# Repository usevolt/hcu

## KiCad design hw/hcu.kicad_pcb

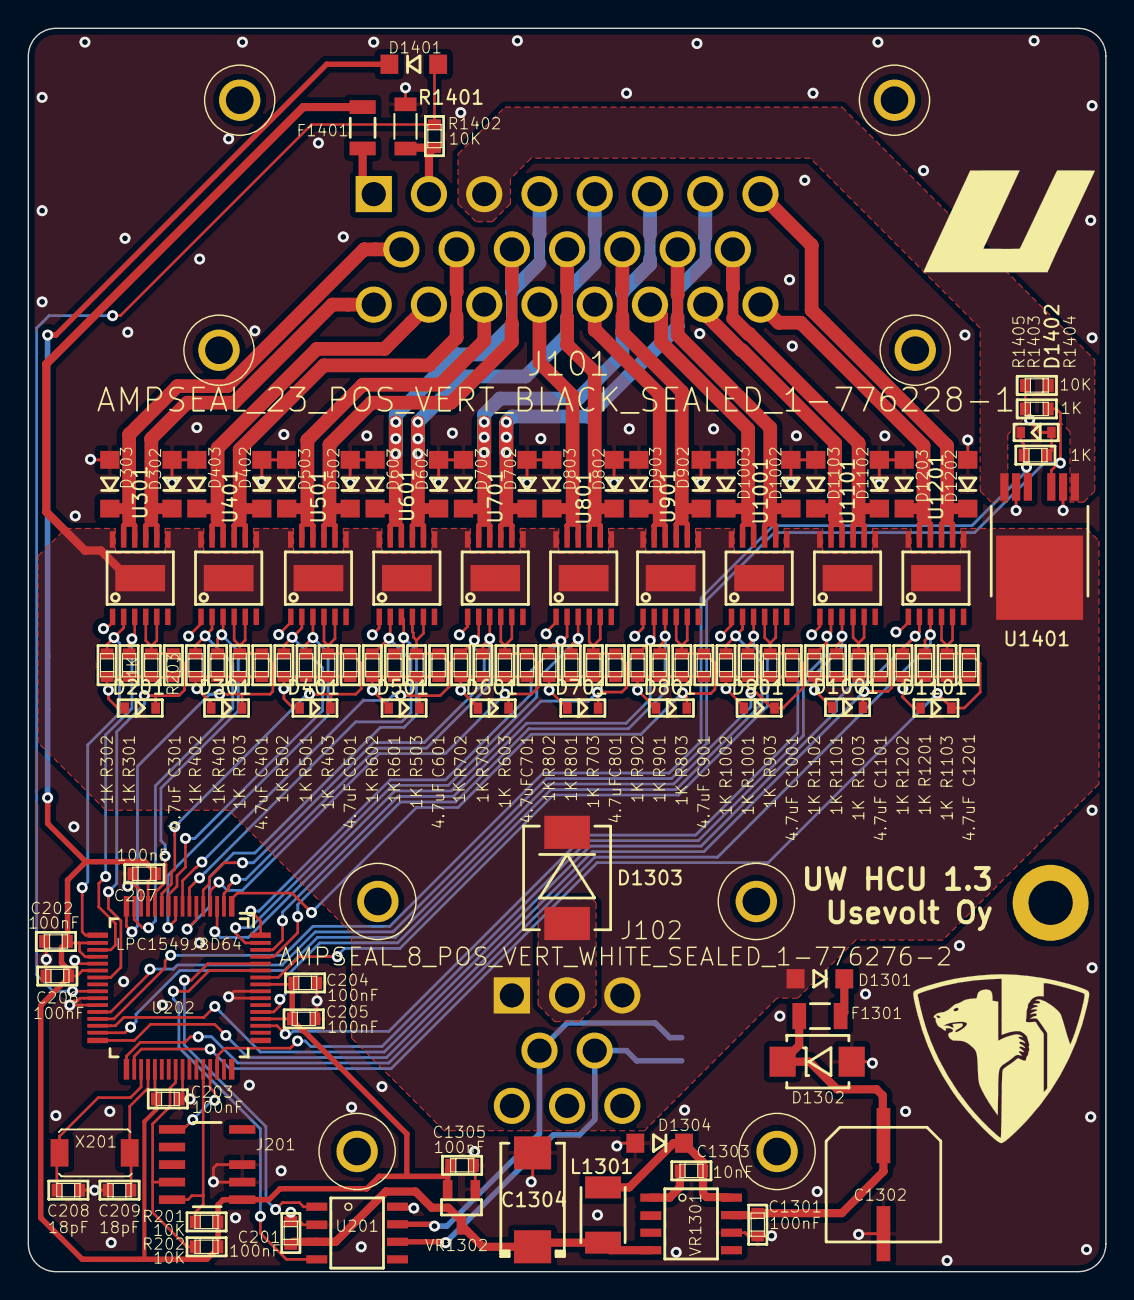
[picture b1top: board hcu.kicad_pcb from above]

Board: 2 copper layers, 78.0 x 90.0 mm, 120 parts (1 on the bottom side), 73 nets.

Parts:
C201, C202, C203, C204, C205, C206, C207, C1301, C1305: 100nF; 0603
C208, C209: 18pF; 0603
C301, C401, C501, C601, C701, C801, C901, C1001, C1101, C1201: 4.7uF; 0603
C1302: CAP_EEE-FK1H470P
C1303: 10nF; 0603
C1304: T491D226K035AT; 7343
D201, D301, D401, D501, D601, D701, D801, D901, D1001, D1101, D1402: ZENER_MM3Z3V6T1G; SOD-323
D302, D303, D402, D403, D502, D503, D602, D603, D702, D703, D802, D803, D902, D903, D1002, D1003, D1102, D1103, D1202, D1203, D1301, D1304, D1401: DIODE_RS07J-GS18; DO219AB
D1302: DIODE_TVS_SMBJ33A-TRDO-214AA; DO-214AA
D1303: DIODE_TVS_TPSMD28A; DO-214AB
F1301, F1401: FUSE_MC36211_350MA; FUSE_MC36211
J101: AMPSEAL_23_POS_VERT_BLACK_SEALED_1-776228-1; AMPSEAL_23_POS_776200-1
J102: AMPSEAL_8_POS_VERT_WHITE_SEALED_1-776276-2; AMPSEAL_8_POS_776275-1
J201: ARM_JTAG_SWD_HEADER_10_PINSMD; ARM_10_PIN_JTAG_SWD_CONNECTOR
L1301: IND_744045210
R1: 120; 0603
R201, R202, R1402, R1405: 10K; 0603
R203, R301, R302, R303, R401, R402, R403, R501, R502, R503, R601, R602, R603, R701, R702, R703, R801, R802, R803, R901, R902, R903, R1001, R1002, R1003, R1101, R1102, R1103, R1201, R1202, R1403, R1404: 1K; 0603
R1401: R_75OHM; 1206
U201: MCP2551_SOIC8; SOIC8
U202: LPC1549JBD64; QFP64
U301, U401, U501, U601, U701, U801, U901, U1001, U1101, U1201: VND5050AJTR-E; PowerSSO-12
U1401: VN5E010AH; HPAK
VR1301: LM2671SOIC8; SOIC8
VR1302: REG_MCP1700; SOT-23_3-PIN
X201: XTAL_7A-12.000MAAJ-T; XTAL_7A-20.000MAJ

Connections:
+3V3: C202.1, C203.1, C204.1, C205.1, C206.1, C207.1, C1305.1, D1401.P$2, J201.P$1, R201.2, R202.2, U202.P$13, U202.P$18, U202.P$20, U202.P$22, U202.P$37, U202.P$52, U202.P$57, VR1302.2
+5V: C201.1, C1304.+, L1301.2, U201.3, VR1301.4, VR1302.3
/Sheet5A8D8BD1/IN1: R401.2, U202.P$12, U401.3
/Sheet5A8D8BD1/IN2: R402.2, U202.P$15, U401.2
/Sheet5A8D8BD1/OUT1: D402.P$2, J101.10, U401.8, U401.9
/Sheet5A8D8BD1/OUT2: D403.P$2, J101.17, U401.10, U401.11
/Sheet5A8D9C63/IN1: R701.2, U202.P$2, U701.3
/Sheet5A8D9C63/IN2: R702.2, U202.P$5, U701.2
/Sheet5A8D9C63/OUT1: D702.P$2, J101.7, U701.8, U701.9
/Sheet5A8D9C63/OUT2: D703.P$2, J101.6, U701.10, U701.11
/Sheet5A8D95F2/IN1: R601.2, U202.P$6, U601.3
/Sheet5A8D95F2/IN2: R602.2, U202.P$7, U601.2
/Sheet5A8D95F2/OUT1: D602.P$2, J101.5, U601.8, U601.9
/Sheet5A8D95F2/OUT2: D603.P$2, J101.4, U601.10, U601.11
/Sheet5A8D785F/IN1: R301.2, U202.P$19, U301.3
/Sheet5A8D785F/IN2: R302.2, U202.P$17, U301.2
/Sheet5A8D785F/OUT1: D302.P$2, J101.16, U301.8, U301.9
/Sheet5A8D785F/OUT2: D303.P$2, J101.9, U301.10, U301.11
/Sheet5A8D900E/IN1: R501.2, U202.P$9, U501.3
/Sheet5A8D900E/IN2: R502.2, U202.P$10, U501.2
/Sheet5A8D900E/OUT1: D502.P$2, J101.11, U501.8, U501.9
/Sheet5A8D900E/OUT2: D503.P$2, J101.18, U501.10, U501.11
/Sheet5A8DA46D/IN1: R801.2, U202.P$63, U801.3
/Sheet5A8DA46D/IN2: R802.2, U202.P$64, U801.2
/Sheet5A8DA46D/OUT1: D802.P$2, J101.12, U801.8, U801.9
/Sheet5A8DA46D/OUT2: D803.P$2, J101.19, U801.10, U801.11
/Sheet5A8DB2AC/IN1: R901.2, U202.P$61, U901.3
/Sheet5A8DB2AC/IN2: R902.2, U202.P$62, U901.2
/Sheet5A8DB2AC/OUT1: D902.P$2, J101.13, U901.8, U901.9
/Sheet5A8DB2AC/OUT2: D903.P$2, J101.20, U901.10, U901.11
/Sheet5A8DBBEE/IN1: R1001.2, U202.P$58, U1001.3
/Sheet5A8DBBEE/IN2: R1002.2, U202.P$53, U1001.2
/Sheet5A8DBBEE/OUT1: D1002.P$2, J101.14, U1001.8, U1001.9
/Sheet5A8DBBEE/OUT2: D1003.P$2, J101.21, U1001.10, U1001.11
/Sheet5A8DEA05/IN1: R1101.2, U202.P$46, U1101.3
/Sheet5A8DEA05/IN2: R1102.2, U202.P$51, U1101.2
/Sheet5A8DEA05/OUT1: D1102.P$2, J101.15, U1101.8, U1101.9
/Sheet5A8DEA05/OUT2: D1103.P$2, J101.22, U1101.10, U1101.11
/Sheet5A8DF700/IN1: R1201.2, U202.P$33, U1201.3
/Sheet5A8DF700/IN2: R1202.2, U202.P$30, U1201.2
/Sheet5A8DF700/OUT1: D1202.P$2, J101.8, U1201.8, U1201.9
/Sheet5A8DF700/OUT2: D1203.P$2, J101.23, U1201.10, U1201.11
/Sheet5ABCCFA6/IN1: R1403.2, U202.P$28, U1401.3
/Sheet5ABCCFA6/OUT1: J101.3, R1405.2, U1401.1, U1401.7
/Sheet5AC56778/PRESS_IN: J101.2, R1401.1, R1402.2
/Sheet5AC56778/PRESS_SENSE: D1401.P$1, R1402.1, U202.P$25
/Sheet5AC56778/PRESS_VDD: F1401.P$1, J101.1
/lpc1549/CANH: J102.4, R1.1, U201.7
/lpc1549/CANL: J102.5, R1.2, U201.6
/lpc1549/CAN_RX: U201.4, U202.P$59
/lpc1549/CAN_TX: U201.1, U202.P$60
/lpc1549/OUT1_SENSE: C301.2, D201.1, R203.1, U202.P$23, U301.4, U301.5
/lpc1549/OUT2_SENSE: C401.2, D301.1, R303.1, U202.P$16, U401.4, U401.5
/lpc1549/OUT3_SENSE: C501.2, D401.1, R403.1, U202.P$11, U501.4, U501.5
/lpc1549/OUT4_SENSE: C601.2, D501.1, R503.1, U202.P$8, U601.4, U601.5
/lpc1549/OUT5_SENSE: C701.2, D601.1, R603.1, U202.P$4, U701.4, U701.5
/lpc1549/OUT6_SENSE: C801.2, D701.1, R703.1, U202.P$3, U801.4, U801.5
/lpc1549/OUT7_SENSE: C901.2, D801.1, R803.1, U202.P$1, U901.4, U901.5
/lpc1549/OUT8_SENSE: C1001.2, D901.1, R903.1, U202.P$31, U1001.4, U1001.5
/lpc1549/OUT9_SENSE: C1101.2, D1001.1, R1003.1, U202.P$32, U1101.4, U1101.5
/lpc1549/OUT10_SENSE: C1201.2, D1101.1, R1103.1, U202.P$34, U1201.4, U1201.5
/lpc1549/OUT11_SENSE: D1402.1, R1404.1, U202.P$29, U1401.5
/lpc1549/RESET: J201.P$9, U202.P$45
GND: C201.2, C202.2, C203.2, C204.2, C205.2, C206.2, C207.2, C208.2, C209.2, C301.1, C401.1, C501.1, C601.1, C701.1, C801.1, C901.1, C1001.1, C1101.1, C1201.1, C1301.2, C1302.-, C1304.-, C1305.2, D201.2, D301.2, D302.P$1, D303.P$1, D401.2, D402.P$1, D403.P$1, D501.2, D502.P$1, D503.P$1, D601.2, D602.P$1, D603.P$1, D701.2, D702.P$1, D703.P$1, D801.2, D802.P$1, D803.P$1, D901.2, D902.P$1, D903.P$1, D1001.2, D1002.P$1, D1003.P$1, D1101.2, D1102.P$1, D1103.P$1, D1202.P$1, D1203.P$1, D1302.P$1, D1303.1, D1304.P$1, D1402.2, J102.2, J201.P$3, J201.P$5, R203.2, R301.1, R302.1, R303.2, R401.1, R402.1, R403.2, R501.1, R502.1, R503.2, R601.1, R602.1, R603.2, R701.1, R702.1, R703.2, R801.1, R802.1, R803.2, R901.1, R902.1, R903.2, R1001.1, R1002.1, R1003.2, R1101.1, R1102.1, R1103.2, R1201.1, R1202.1, R1401.2, R1403.1, R1404.2, R1405.1, U201.2, U201.8, U202.P$14, U202.P$21, U202.P$26, U202.P$27, U202.P$41, U202.P$55, U202.P$56, U301.1, U401.1, U501.1, U601.1, U701.1, U801.1, U901.1, U1001.1, U1101.1, U1201.1, U1401.2, U1401.6, VR1301.6, VR1302.1
unnamed: C208.1, U202.P$35, X201.P$1
unnamed: C209.1, U202.P$36, X201.P$2
unnamed: C1301.1, C1302.+, D1302.P$2, F1301.P$2, VR1301.7
unnamed: C1303.1, VR1301.1
unnamed: C1303.2, D1304.P$2, L1301.1, VR1301.8
unnamed: D1301.P$2, F1301.P$1
unnamed: J201.P$2, R201.1, U202.P$44
unnamed: J201.P$4, R202.1, U202.P$40
VDD: D1301.P$1, D1303.2, F1401.P$2, J102.1, J102.3, U301.7, U301.12, U301.13, U401.7, U401.12, U401.13, U501.7, U501.12, U501.13, U601.7, U601.12, U601.13, U701.7, U701.12, U701.13, U801.7, U801.12, U801.13, U901.7, U901.12, U901.13, U1001.7, U1001.12, U1001.13, U1101.7, U1101.12, U1101.13, U1201.7, U1201.12, U1201.13, U1401.4

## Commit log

2018-02-06 hcu initial revision
2018-03-30 1.0 pcb created
2018-04-24 first revision ordered from seeed
2018-07-01 hw 2.0.0 ordered
2018-07-01 ampseal 8 pin changed to white one
2018-07-04 enclosure 3.0, for cnc machining ready
2018-07-30 ready for boom lift, fold & rotate testing
2018-08-07 boom and legs work ,pressure no
2018-08-10 ready for testing
2018-08-11 memory reduced for step task
2018-08-15 pull down resistor and flyback diode added to out11
2018-09-09 CM_6.2.1 delivered, first customer machine with CCU, HCU & ICU
2018-09-13 disabling modules also clears the requests
2018-09-18 boom telescope mapped to right keypad button
2018-09-25 impl2 mapped to left joy z when uw100 is selected, for mense cutter
2018-10-04 sense protection diodes changed to zeners
2018-11-02 mutex added to main in order to prevent occassional movement freezing
2018-11-07 enclosure ready for cnc'd, added heatsink to mosfets
2018-11-13 boom telescope implemented
2018-11-22 possible hardfault fix:
    interrupts disabled when accessing PDO parameters
2018-11-30 hal updated to latest uv bootloader
2018-12-21 pcb 1.2.0 created, with heatsink attachment hole
2019-01-02 trying to fix a bug regarding when some movements are left on
2019-01-02 step funciton priority is bigger than solenoid_step
2019-01-21 ce mark added
2019-01-24 pcb 1.3.0 created
2019-02-10 wdt implemented to prevent freezing with all movements ON
2019-02-19 movement freezing debug messages removed
2019-03-19 updated hal
2019-04-07 dual_solenoid_output direction freezing bugfix
2019-06-09 boom rotate disabled while driving when back steering is enabled
2019-07-29 hcu hydrout implement added
2019-08-09 printf debug removed from boom_telescope
2019-08-23 major bugfix: hcu restarting fixed by disabling interrupts when adc is making a conversion
2019-09-10 Major bugfix: pressure sensing uses median adc reading to prevent glitches
2019-09-10 complies with uw180s icu tilt on right keypad button 7:
    boom telescope is on left thumb on uw180s
2019-09-19 190919: sent hyd freezing bugfix via email
2019-10-09 submodule urls set to https github
2019-10-10 terminal disabled at init
2020-04-29 seal created for enclosure
2020-07-07 IMPL2 control with canreq implemented
2020-07-09 D4wd control enabled when door or seat sw are active
2020-08-05 boom telescope enabled and moved to left joystick buttons
2020-12-28 work rpm req implemented for stage5 engine
2021-01-04 rotator activates work
2021-01-09 assembly directory added for enclosure files
2021-01-11 keypad heratbeat delay time increased to 2200 ms to prevent d4wd sticking
2021-04-09 hcu.json bugfix
2021-07-02 020721: remotely fixed impl2 acceleration ramp
